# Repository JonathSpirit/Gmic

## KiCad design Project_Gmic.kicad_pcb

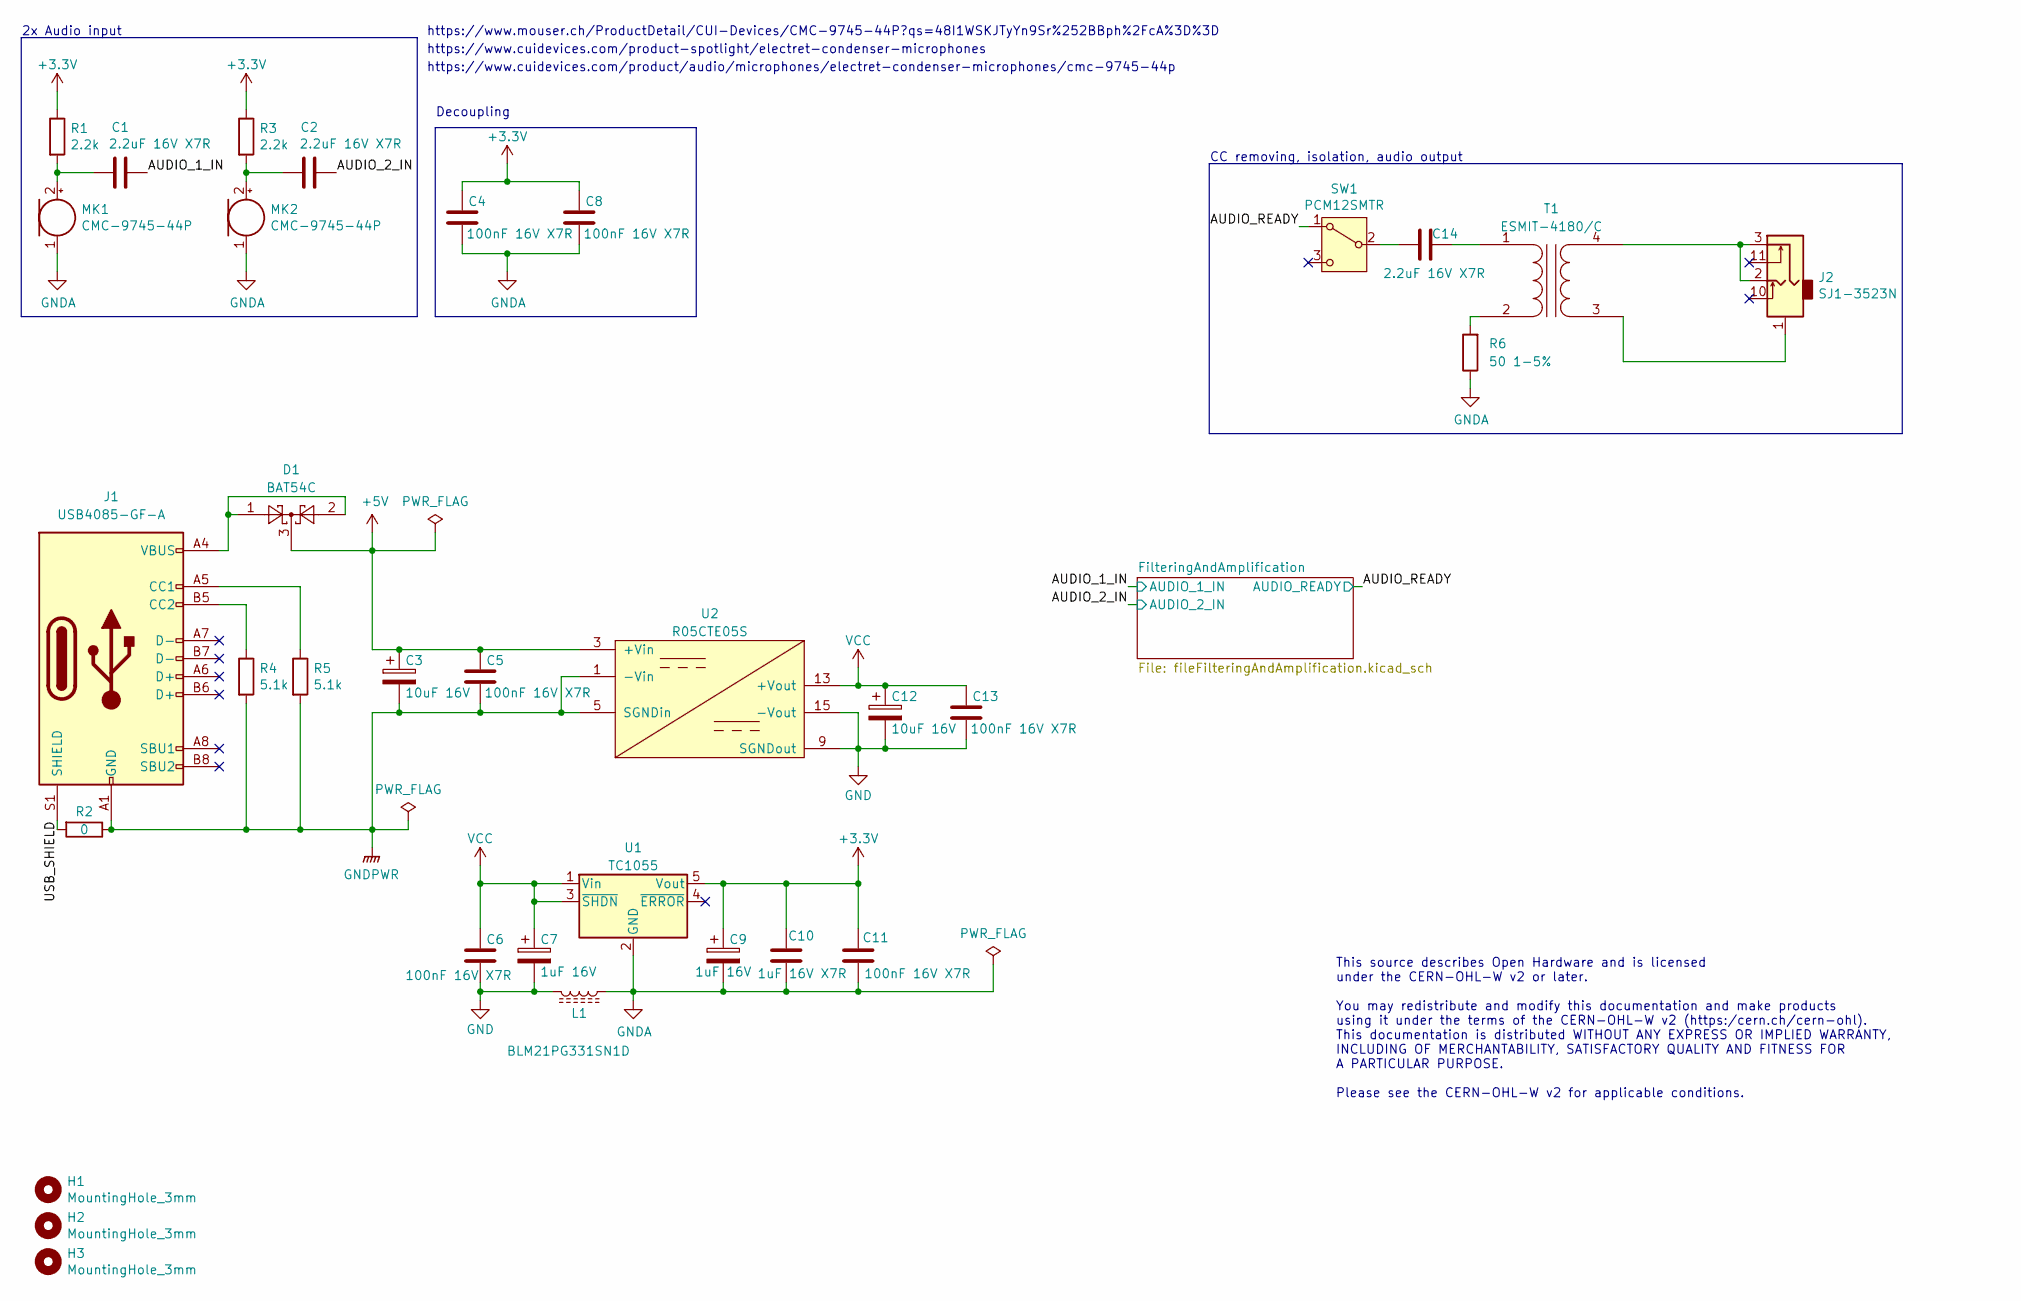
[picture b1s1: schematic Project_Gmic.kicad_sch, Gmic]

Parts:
C1, C2, C14: 2.2uF 16V X7R; C_0805_2012Metric
C3, C12: 10uF 16V; CP_Elec_4x5.4
C4, C5, C6, C8, C11, C13: 100nF 16V X7R; C_0805_2012Metric
C7, C9: 1uF 16V; CP_Elec_4x5.4
C10: 1uF 16V X7R; C_0805_2012Metric
D1: BAT54C; SOT-23
H1, H2, H3: MountingHole_3mm
J1: USB4085-GF-A; USB_C_Receptacle_GCT_USB4085
J2: SJ1-3523N; SJ13523N
L1: BLM21PG331SN1D; L_0805_2012Metric
MK1, MK2: CMC-9745-44P; CMC974544P
R1, R3: 2.2k; R_0805_2012Metric
R2: 0; R_0805_2012Metric
R4, R5: 5.1k; R_0805_2012Metric
R6: 50 1-5%; R_0805_2012Metric
SW1: PCM12SMTR; SW_SPDT_PCM12
T1: ESMIT-4180/C; SOP254P914X350-4N
U1: TC1055; SOT-23-5
U2: R05CTE05S; SOIC-16W_7.5x10.3mm_P1.27mm

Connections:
+3.3V: C4.1, C8.1, C9.1, C10.1, C11.1, R1.1, R3.1, U1.5 (Vout); also elsewhere on the board
+5V: C3.1, C5.1, D1.3, U2.3 (+Vin), U2.4 (+Vin)
/AUDIO_1_IN: C1.1; also elsewhere on the board
/AUDIO_2_IN: C2.1; also elsewhere on the board
/AUDIO_READY: SW1.1 (A); also elsewhere on the board
/USB_SHIELD: J1.S1 (SHIELD), R2.2
GND: C6.2, C7.2, C12.2, C13.2, L1.2, U2.9 (SGNDout), U2.11 (SGNDout), U2.12 (SGNDout), U2.15 (-Vout), U2.16 (-Vout)
GNDA: C4.2, C8.2, C9.2, C10.2, C11.2, L1.1, MK1.1 (-), MK2.1 (-), R6.1, U1.2 (GND); also elsewhere on the board
GNDPWR: C3.2, C5.2, J1.A1 (GND), J1.A12 (GND), J1.B1 (GND), J1.B12 (GND), R2.1, R4.2, R5.2, U2.1 (-Vin), U2.2 (-Vin), U2.5 (SGNDin), U2.6 (SGNDin), U2.7 (SGNDin), U2.8 (SGNDin)
unnamed: D1.1, D1.2, J1.A4 (VBUS), J1.A9 (VBUS), J1.B4 (VBUS), J1.B9 (VBUS)
unnamed: J1.A5 (CC1), R5.1
unnamed: J1.B5 (CC2), R4.1
unnamed: C1.2, MK1.2 (+), R1.2
unnamed: C2.2, MK2.2 (+), R3.2
unnamed: C14.2, SW1.2 (B)
unnamed: C14.1, T1.1 (AA)
unnamed: R6.2, T1.2 (AB)
unnamed: J2.1, T1.3 (SA)
unnamed: J2.2, J2.3, T1.4 (SB)
VCC: C6.1, C7.1, C12.1, C13.1, U1.1 (Vin), U1.3 (~SHDN), U2.13 (+Vout), U2.14 (+Vout)

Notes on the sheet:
https://www.mouser.ch/ProductDetail/CUI-Devices/CMC-9745-44P?qs=48I1WSKJTyYn9Sr%252BBph%2FcA%3D%3D
CC removing, isolation, audio output
https://www.cuidevices.com/product/audio/microphones/electret-condenser-microphones/cmc-9745-44p
Decoupling
https://www.cuidevices.com/product-spotlight/electret-condenser-microphones
2x Audio input
This source describes Open Hardware and is licensed under the CERN-OHL-W v2 or later. You may redistribute and modify this documentation and make products using it under the terms of the CERN-OHL-W v2 (https:/cern.ch/cern-ohl). This documentation is distributed WITHOUT ANY EXPRESS OR IMPLIED WARRAN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

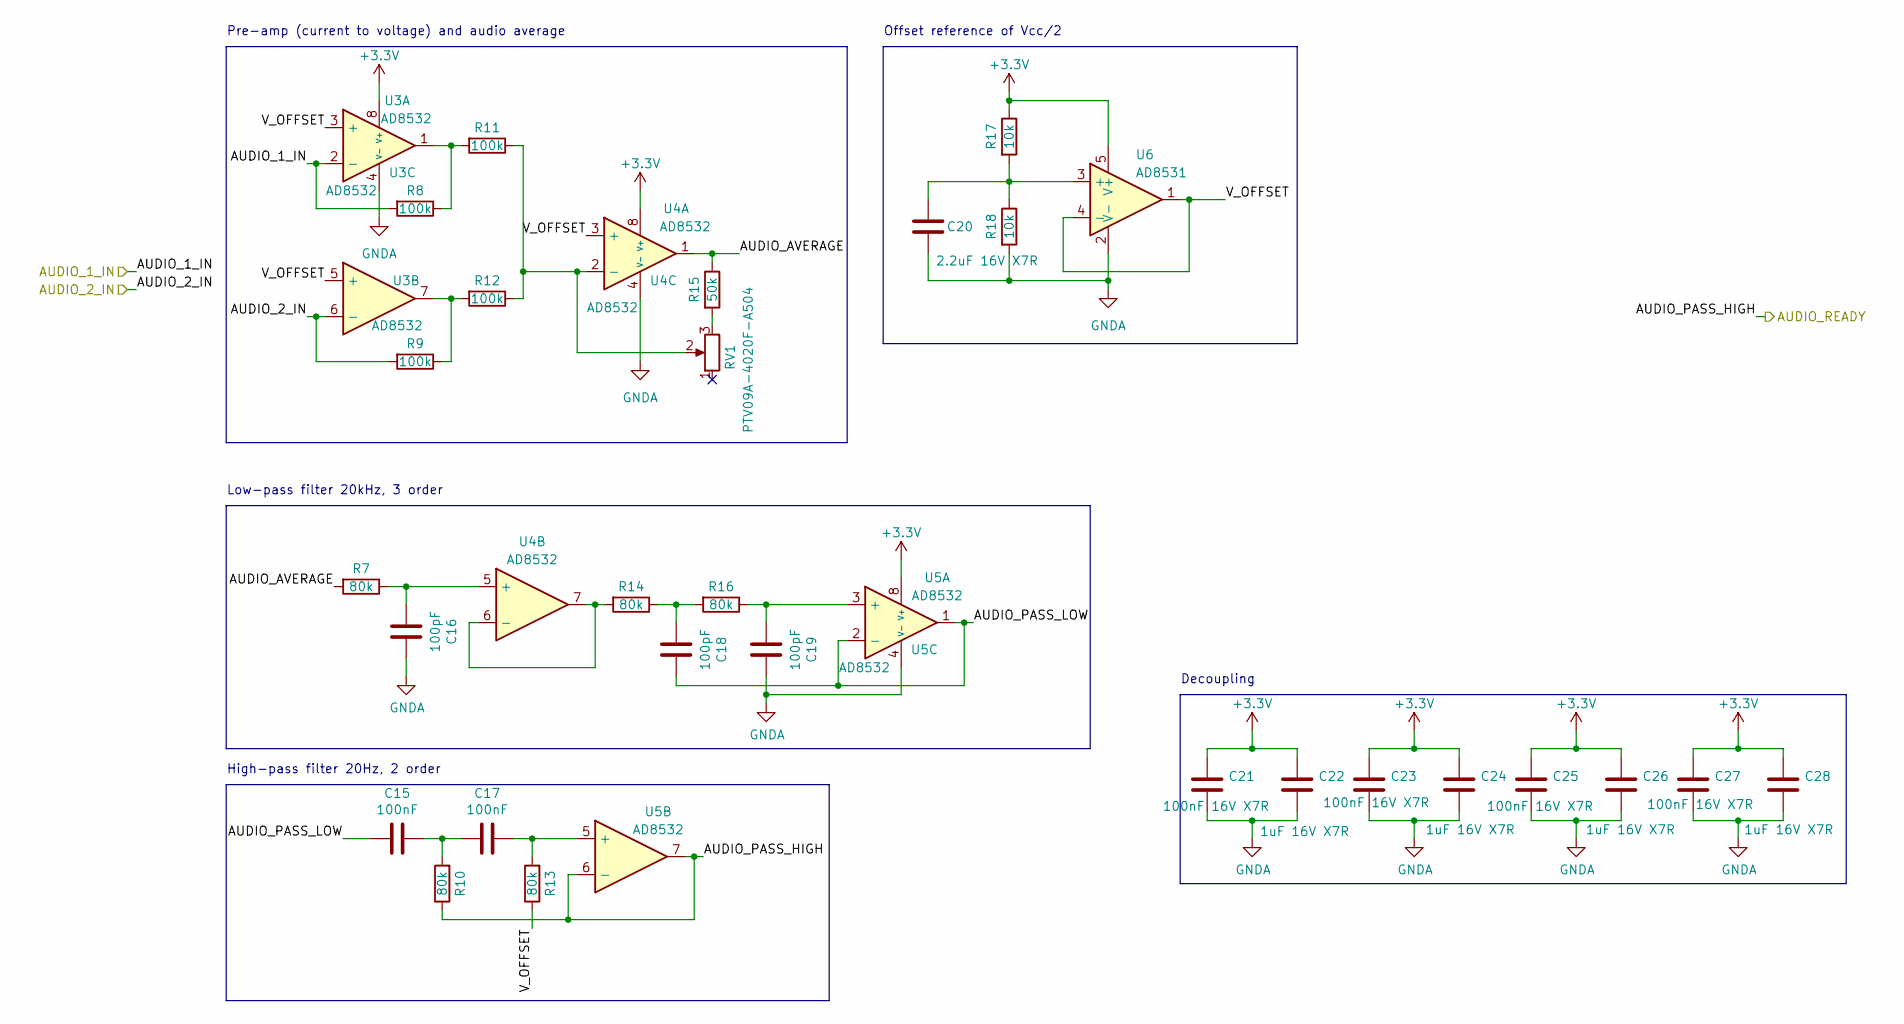
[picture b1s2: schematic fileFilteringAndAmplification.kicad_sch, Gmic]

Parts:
C15, C17: 100nF; C_1206_3216Metric
C16, C18, C19: 100pF; C_0805_2012Metric
C20: 2.2uF 16V X7R; C_0805_2012Metric
C21, C23, C25, C27: 100nF 16V X7R; C_0805_2012Metric
C22, C24, C26, C28: 1uF 16V X7R; C_0805_2012Metric
R7, R10, R13, R14, R16: 80k; R_0805_2012Metric
R8, R9, R11, R12: 100k; R_0805_2012Metric
R15: 50k; R_0805_2012Metric
R17, R18: 10k; R_0805_2012Metric
RV1: PTV09A-4020F-A504; PTV09A-4
U3, U4, U5: AD8532; SOIC-8_3.9x4.9mm_P1.27mm
U6: AD8531; SOT-23-5

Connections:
+3.3V: C21.1, C22.1, C23.1, C24.1, C25.1, C26.1, C27.1, C28.1, R17.1, U3.8 (V+), U4.8 (V+), U5.8 (V+), U6.5 (V+); also elsewhere on the board
/AUDIO_1_IN: R8.2, U3.2 (-); also elsewhere on the board
/AUDIO_2_IN: R9.2, U3.6 (-); also elsewhere on the board
/AUDIO_READY: R10.1, U5.6 (-), U5.7; also elsewhere on the board
/FilteringAndAmplification/AUDIO_AVERAGE: R7.2, R15.1, U4.1
/FilteringAndAmplification/AUDIO_PASS_LOW: C15.2, C18.1, U5.1, U5.2 (-)
/FilteringAndAmplification/V_OFFSET: R13.1, U3.3 (+), U3.5 (+), U4.3 (+), U6.1, U6.4 (-)
GNDA: C16.1, C19.1, C20.2, C21.2, C22.2, C23.2, C24.2, C25.2, C26.2, C27.2, C28.2, R18.2, U3.4 (V-), U4.4 (V-), U5.4 (V-), U6.2 (V-); also elsewhere on the board
unnamed: C15.1, C17.2, R10.2
unnamed: C18.2, R14.1, R16.2
unnamed: R8.1, R11.2, U3.1
unnamed: R9.1, R12.2, U3.7
unnamed: R15.2, RV1.3
unnamed: R11.1, R12.1, RV1.2, U4.2 (-)
unnamed: C16.2, R7.1, U4.5 (+)
unnamed: R14.2, U4.6 (-), U4.7
unnamed: C19.2, R16.1, U5.3 (+)
unnamed: C17.1, R13.2, U5.5 (+)
unnamed: C20.1, R17.2, R18.1, U6.3 (+)

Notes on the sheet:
Decoupling
High-pass filter 20Hz, 2 order
Pre-amp (current to voltage) and audio average
Low-pass filter 20kHz, 3 order
Offset reference of Vcc/2

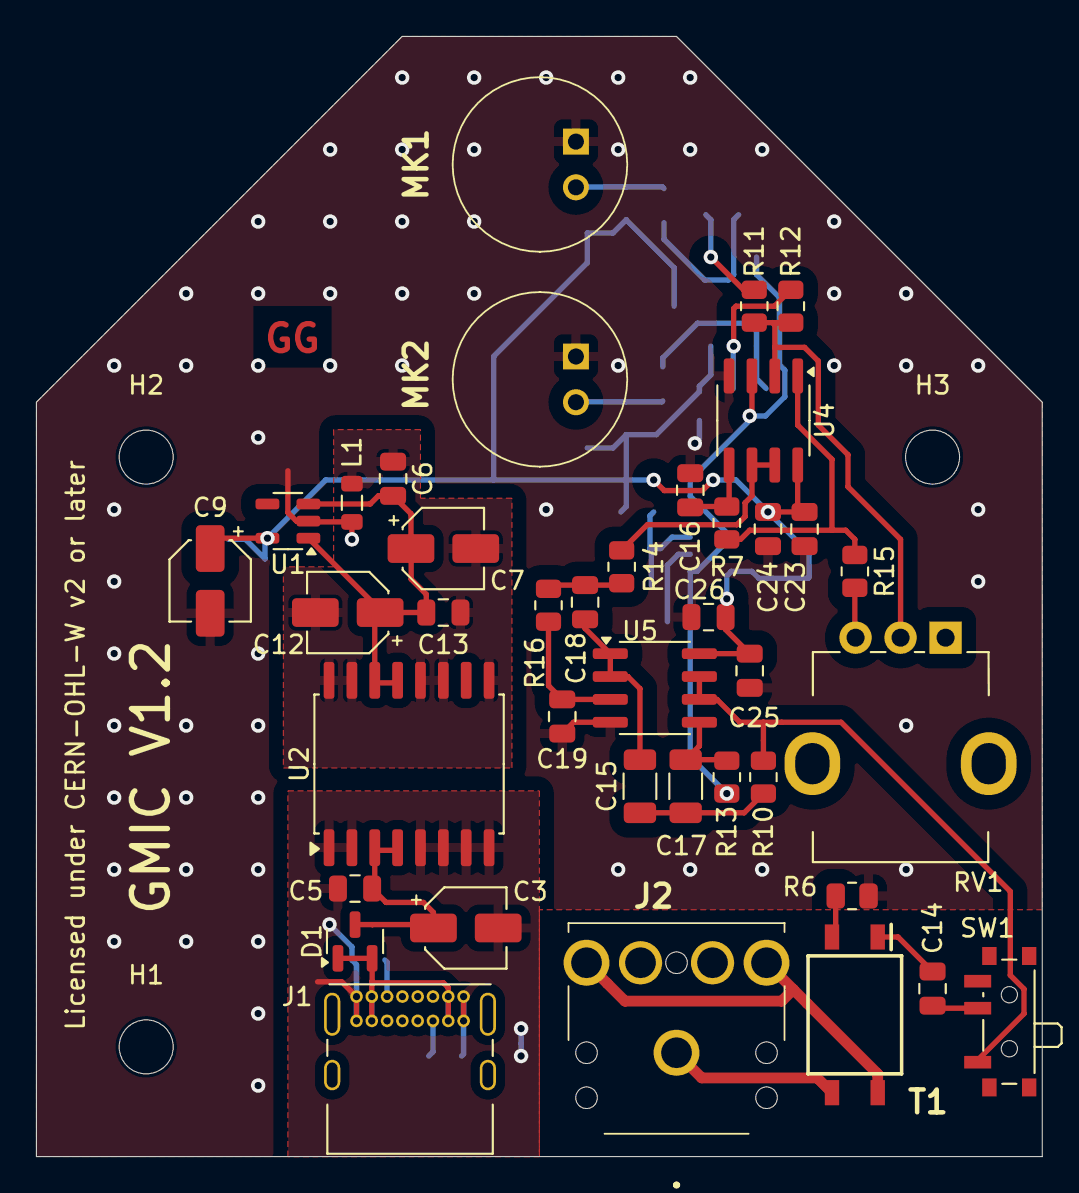
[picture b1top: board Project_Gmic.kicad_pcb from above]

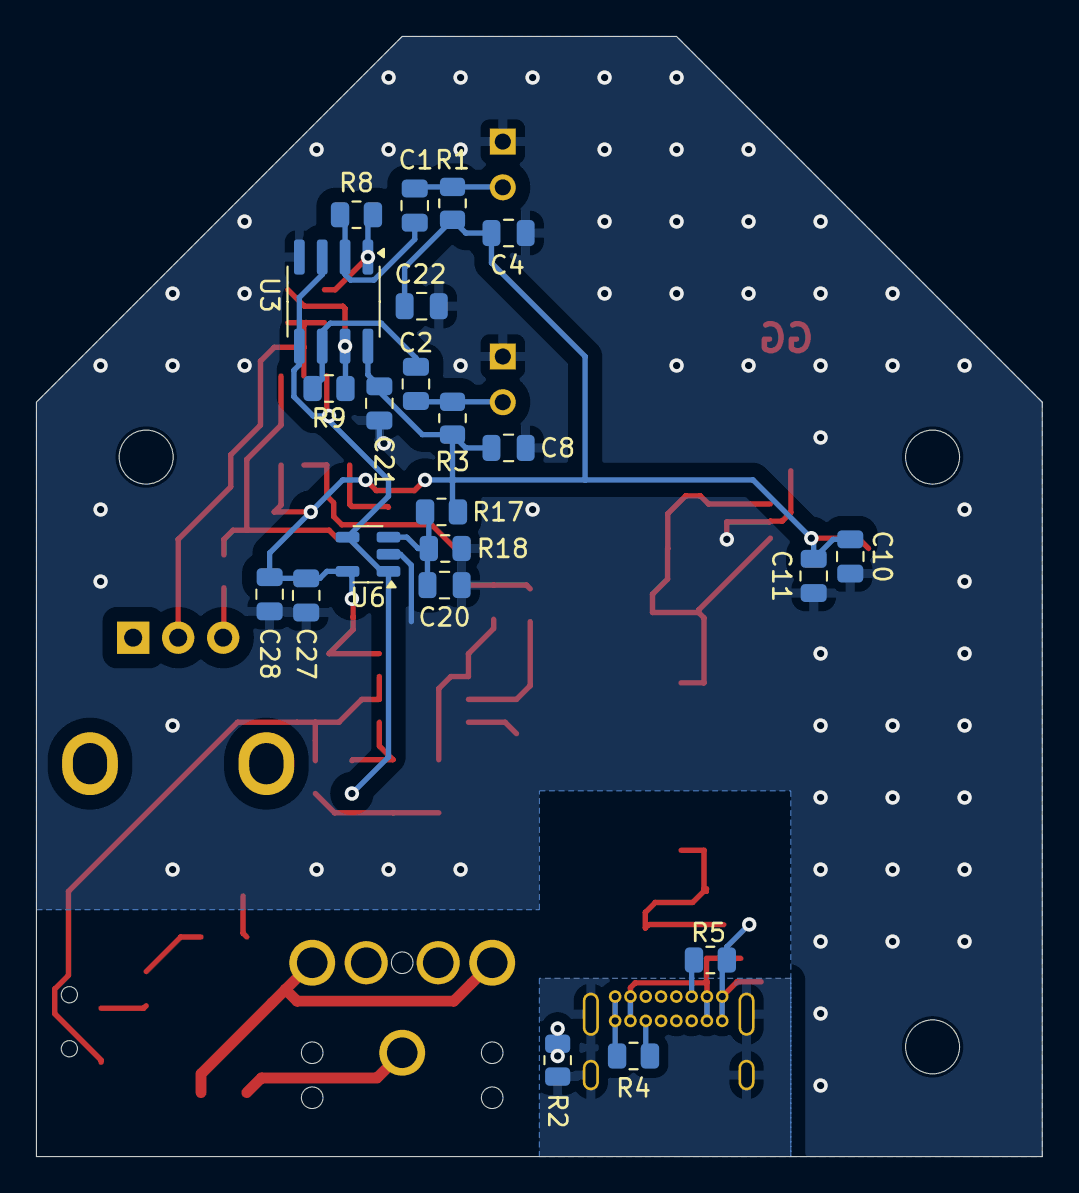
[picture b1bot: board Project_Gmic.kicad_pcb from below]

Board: 2 copper layers, 55.9 x 62.2 mm, 64 parts (22 on the bottom side), 34 nets.

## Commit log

2022-03-04 Initial WIP release
2022-03-05 butterworth filter, new aop, cleaning
2022-03-06 Set connectors, preparing usb-c
2022-03-10 Add better microphones simulation model
2022-05-13 Schematics improvement, file cleaning
2022-05-13 Searching for parts
2022-05-13 First iteration of the PCB, Rpot
2022-05-14 Changing the potentiometer, finishing placement and board
2022-05-18 BOM, finishing PCB, changing some non-available components
2022-05-18 add link
2022-06-21 Finalizing PCB, gerbert file
2023-03-16 moving to kicad 7, redo simulations WIP
2023-03-16 finishing the simulation, began schematic
2023-03-16 updating schematic, updating BOM
2023-03-16 remove old custom lib
2023-03-16 update PCB, finish placement and first routing
2023-03-17 fixing pcb error, reset footprints from libs, add diode
2023-03-18 finishing PCB, fix serigraph, complete BOM, fix some non-sense in footprints
2023-03-23 moving mounting holes, fixing POT footprint, exporting fabrication files
2024-09-21 working on a v1.2, better USB isolation, audio output isolation
2024-10-30 placement, BOM inside kicad
2024-10-31 first step final
2025-03-14 generate gerbert files

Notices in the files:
Project_Gmic.kicad_pcb:
Copyright Guillaume Guillet 2024
Licensed under CERN-OHL-W v2 or later
